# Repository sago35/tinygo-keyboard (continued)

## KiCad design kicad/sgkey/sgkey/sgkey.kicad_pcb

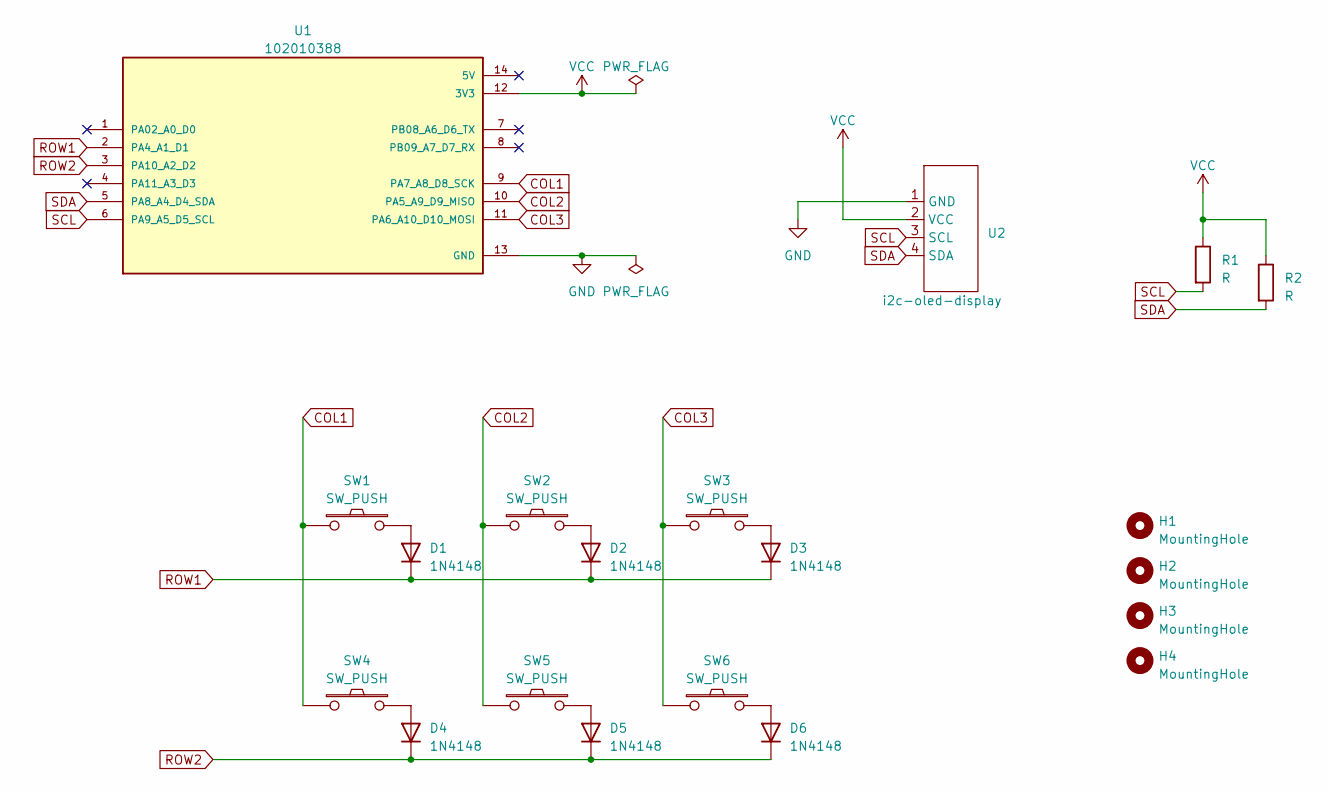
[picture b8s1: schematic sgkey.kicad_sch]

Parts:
D1, D2, D3, D4, D5, D6: 1N4148; D_DO-35_SOD27_P7.62mm_Horizontal
H1, H2, H3, H4: MountingHole; MountingHole_2.2mm_M2
R1, R2: R; R_Axial_DIN0204_L3.6mm_D1.6mm_P7.62mm_Horizontal
SW1, SW2, SW3, SW4, SW5, SW6: SW_PUSH; CherryMX_ChocV2_1u
U1: 102010388; MODULE_102010388; PARTREV N/A
U2: i2c-oled-display; i2c-oled-display-0.96

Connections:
COL1: SW1.1, SW4.1, U1.9 (PA7_A8_D8_SCK)
COL2: SW2.1, SW5.1, U1.10 (PA5_A9_D9_MISO)
COL3: SW3.1, SW6.1, U1.11 (PA6_A10_D10_MOSI)
GND: U1.13 (GND), U2.1 (GND)
unnamed: D1.2 (A), SW1.2
unnamed: D2.2 (A), SW2.2
unnamed: D3.2 (A), SW3.2
unnamed: D4.2 (A), SW4.2
unnamed: D5.2 (A), SW5.2
unnamed: D6.2 (A), SW6.2
ROW1: D1.1 (K), D2.1 (K), D3.1 (K), U1.2 (PA4_A1_D1)
ROW2: D4.1 (K), D5.1 (K), D6.1 (K), U1.3 (PA10_A2_D2)
SCL: R1.2, U1.6 (PA9_A5_D5_SCL), U2.3 (SCL)
SDA: R2.2, U1.5 (PA8_A4_D4_SDA), U2.4 (SDA)
VCC: R1.1, R2.1, U1.12 (3V3), U2.2 (VCC)

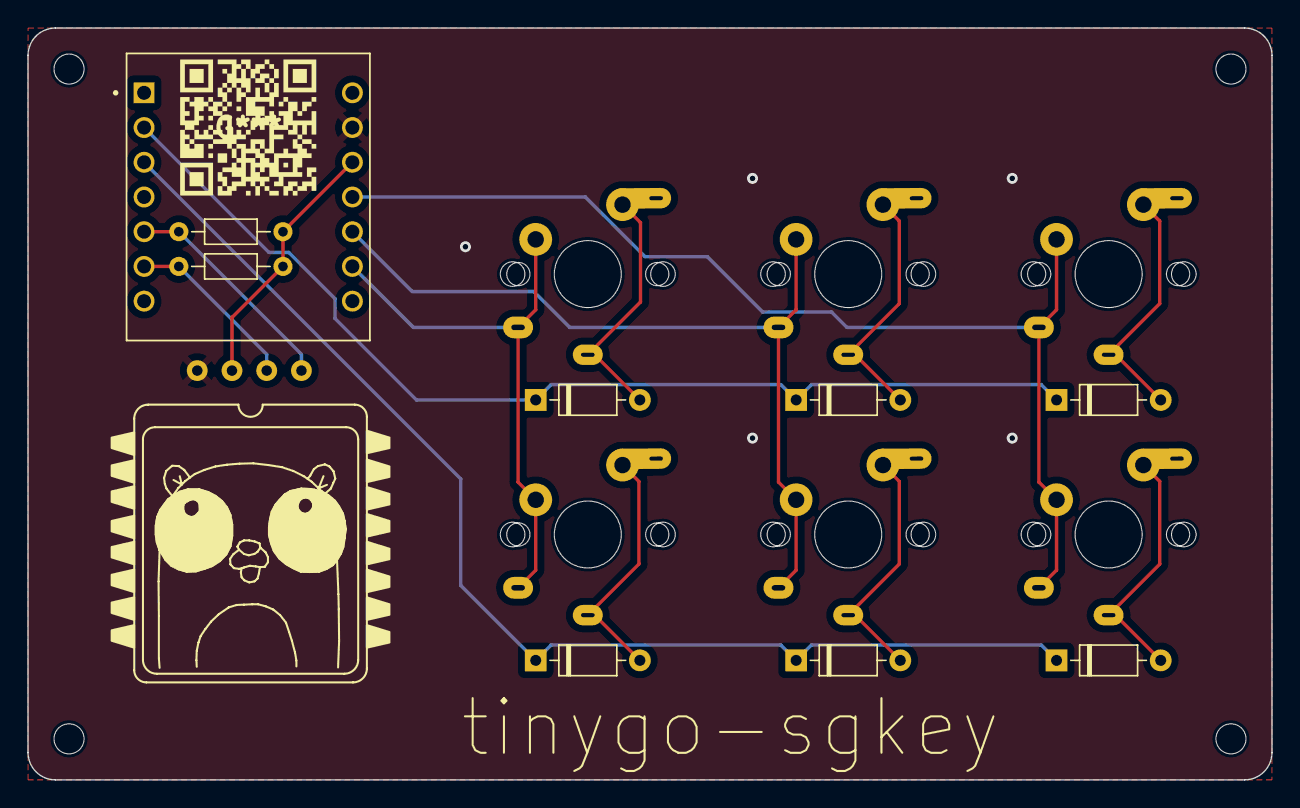
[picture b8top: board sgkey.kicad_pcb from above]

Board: 2 copper layers, 91.0 x 55.0 mm, 20 parts (0 on the bottom side), 15 nets.

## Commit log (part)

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2023-03-24 Fix behavior of `mod + ctrl`
2023-03-24 Add ./kicad
2023-03-24 Add Makefile
2023-03-24 Add kiicad/sgkey and kicad/wiokey
2023-03-24 Add smoketest
2023-04-04 Add fric10key
2023-04-08 Update ./targets/sgkb/left
2023-04-08 Add .gitignore
2023-04-09 Refactor (#2)
    refactor
2023-04-09 Add GpioKeyboard
2023-04-09 Add RotaryKeyboard
2023-04-09 Fix UartKeyboard
2023-04-10 Fix UartKeyboard state transitions
2023-04-10 Refactor
2023-04-10 Update targets/macropad-rp2040
2023-04-10 Add forward and back buttons to Mouse
2023-04-10 Update targets/sgkb/left
2023-04-13 Add kbmatrix.go
2023-04-13 Add ./targets/fric10key
2023-04-16 Add build tag to kbrotary.go
2023-04-17 Add options.go
2023-04-17 Add build tag
2023-04-17 Add test for `go get`
2023-04-17 Add InvertButtonState option
2023-04-17 Update targets/wiokey
2023-05-18 Update targets/sgkey
2023-05-18 Add InvertDiode option
2023-05-18 Update kicad/wiokey
2023-05-21 Add targets/sgkey/README.md
2023-05-23 Update kicad/sgkb and kicad/sgkb-right
2023-06-08 Add SetCallback()
2023-06-08 go mod
2023-06-08 Add ./targets/gopher-badge
2023-06-13 Fix nil pointer dereference
2023-06-13 Add display support for ./targets/sgkey
2023-06-13 Update README (sgkb-0.3.0)
2023-06-13 Update Makefile
2023-06-13 Update README.md (add gopher-badge)
2023-06-23 Improve key detection by pullups of kbduplexmatrix
2023-07-10 Add kicad/xiao-kb01
2023-07-10 Add kbsquaredmatrix.go
2023-07-10 Add targets/xiao-kb01
2023-07-10 Update targets/xiao-kb01
2023-07-15 Add kicad/xiao-kb01/xiao-kb01-top
2023-07-15 Add kicad/lib/xiao/CherryMX_ChocV2_1u_with_2u_stabilizer
2023-07-15 sgkb 0.4.0
2023-07-16 WIP: targets/sgkey
2023-07-17 MO(0) ～ MO(5) に対応
2023-07-17 WIP: kbd.Load() の引数変更に対応
2023-07-25 sgkb-0.4.0
2023-07-26 Update kicad library path
2023-07-26 Add kicad/lib/xiao/CherryMX_Hotswap_top.kicad_mod
2023-08-04 Support sgkb-0.4.0
2023-08-05 Add targets/sgkb/left-0.3.0
2023-08-05 Update callback
2023-08-05 Update kbuart.go and ./targets/sgkb/right
2023-08-05 WIP: vial
2023-08-06 Add SetKeycode()
2023-08-06 Add keyboardDef to targets/sgkb/left-0.3.0
2023-08-06 Add support for vial (read layout)
2023-08-06 WIP: vial.json を embed で読み込むように修正
2023-08-08 Add vial settings
2023-08-08 Refactor KeyVia()
2023-08-12 Add vial support for ./targets/sgkey
2023-08-14 WIP: save
2023-08-15 Add comment
2023-08-15 Add checks to prevent out-of-index access
2023-08-15 Change to store settings to machine.Flash
2023-08-15 Add TODO comment
2023-08-15 Move flash write to Tick()
2023-08-15 Add vial support to macropad-rp2040 and gopher-badge
2023-08-19 Refactore keybords and keys settings
2023-08-19 Add vial support to ./targets/xiao-kb01
2023-08-19 implement generating def.go
2023-08-19 copy def.go
2023-08-19 add lzma example to ./cmd
2023-08-19 add gen-def command to Makefile
2023-08-19 update keyboard-def
2023-08-19 add gen-def of xiao-kb01
2023-08-19 mkdir ./cmd/gen-def
2023-08-19 add xiao-kb01/def.go
2023-08-20 fix imports
2023-08-20 add `make gen-def-with-find` command
2023-08-20 Add `make gen-def` (#4)
2023-08-23 Remove `//go:embed vial.json`
2023-08-23 Update vial.json (rows / cols)
2023-08-23 Vial (#5)
2023-08-23 Add .github/workflows/ci.yml
2023-08-23 Add .github/workflows/ci.yml (#6)
2023-08-23 Remove heap allocs
2023-08-23 Set keycode 0x7C03 to a special keycode for restoring default
2023-09-01 Optimize number of keys
2023-09-01 Update targets
2023-09-01 Remove unused const value
2023-09-08 Add tutorial
2023-09-14 Add vial support to wiokey
2023-09-14 Add feature to restore key settings to default values
2023-09-15 Add chattering prevention
2023-09-22 Fix chattering prevention without blocking operation for kbduplexmatrix
2023-09-22 Remove blocking oparation
2023-10-10 Improved chattering prevention
2023-10-12 Add kbshifter.go
2023-10-12 Add ./targets/gobadge/
2023-10-17 Consolidate key modifier constants
2023-10-17 Add support for To(x)
2023-10-17 Update targets/gobadge
2023-10-17 vial
2023-10-17 Add Cyclecounter initialization
2023-10-17 Add chattering prevention when changing from None to NoneToPress
2023-10-22 Change variable name
2023-10-30 Add chattering prevention (#13)
    * Add chattering prevention
    * Fix chattering prevention without blocking operation for kbduplexmatrix
    * Remove blocking oparation
    * Improved chattering prevention
    * Add Cyclecounter initialization
    * Add chattering prevention when changing from None to NoneToPress
2023-10-30 Add debounce support for kbgpio, kbmatrix, kbsquaredmatrix
2023-10-30 Add debounce support for kbgpio, kbmatrix, kbsquaredmatrix (#17)
    * Add debounce support for kbgpio, kbmatrix, kbsquaredmatrix
    * fix
2023-10-30 initial bluetooth support between split keyboards
2023-10-31 Extend CI triggers to include pull requests
2023-10-31 Extend CI triggers to include pull requests (#19)
    * Extend CI triggers to include pull requests
2023-10-31 Change to pass through ringbuffer
2023-10-31 WIP: Add targets/sgkey-ble
2023-11-08 go get github.com/bgould/tinygo-rotary-encoder
2023-11-08 Add magic word for vial-gui
2023-11-14 Add ./ble for BLE HID Keyboard
2023-11-14 Remove
2023-11-14 Truncate to 14 characters
2023-11-14 Copy from TinyGo 0.30.0
2023-11-14 Change to send data to blehid instead of usbhid
2023-11-14 Change the reportMap to the same one as used for USB
2023-11-14 Add ./targets/sgkey2
2023-11-16 Update ./targets/sgkey2
2023-11-16 Add ./targets/xiao-kb012/
2023-11-16 Remove comments
2023-12-05 Update ./kicad/lib/
2023-12-05 Add ./kicad/sgh60/
2023-12-05 Add ./targets/sgh60/
2023-12-26 Update ./targets/sgh60/
2023-12-26 Add d.Layer()
2023-12-26 Add ./targets/sgh60/adcdevice.go
2023-12-26 Fix Makefile
2023-12-26 Add ticker for loop interval and removed static sleep in keyboard loop
2023-12-26 Add ./targets/sg48key/
2023-12-26 Add ./targets/sg48key/ (#23)
2023-12-26 Update README.md (#24)
2023-12-26 rename
2023-12-26 Update README.md (#25)
2024-01-01 Refactor keycodes
2024-01-01 Refactor callbacks
2024-01-01 refactor layers
2024-01-01 revert
2024-01-01 Add keyrepeat function to WheelDown / WheelUp
2024-01-16 Several improvements (#26)
    * Changed the timing of callbacks to occur after key processing.
    * Organized key code definitions.
    * Set key repeat for mouse wheel events.
    * Changed the behavior to remember the return destination using a stack when transitioning layers.
2024-01-16 Fix due to debounce not working
2024-01-16 Fix due to debounce not working (#27)
2024-01-30 Change processing interval to 1ms and debounce handling to 1ms x 8 times
2024-01-30 Update ./targets
2024-01-30 Update targets (#29)
2024-01-30 Update kicad/lib/xiao
2024-01-30 Update lib
2024-01-30 Add kicad/sg24key
2024-02-05 Add suport for Vial's Matrix tester
2024-02-05 Add suport for Vial's Matrix tester (#30)
2024-02-15 Add xiao-rp2040 for sg48key, improve joystick
2024-02-15 Add xiao-rp2040 for sg48key, improve joystick (#32)
2024-02-20 Update actions/*
2024-02-20 Update actions/* (#33)
2024-02-28 Add magic word for vial-gui (#21)
2024-02-29 kbrotary: switch to use tinygo-org/drivers v0.27.0
2024-02-29 Add buildtag to kbrotary.go
2024-02-29 kbrotary: switch to use tinygo-org/drivers v0.27.0 (#37)
    * kbrotary: switch to use tinygo-org/drivers v0.27.0
    * go mod
    * Add buildtag to kbrotary.go
2024-02-29 Add CHANGELOG.md
2024-03-19 WIP: BLEHID
2024-04-15 WIP: uart mouse
2024-04-16 Add support for vial macros
2024-04-16 Increase delay for save operation from 500ms to 5000ms
2024-06-17 implemented kbexpander
2024-07-07 Add `Additional Resources` to README.md
2024-07-10 stuff
2024-07-11 updated stuff
2024-07-11 more stuff
2024-07-18 Add device.GetKeyboardCount()
2024-07-18 Add device.GetKeyboardCount() (#43)
2024-07-25 updated module
2024-07-28 Fixed kbexpander and reduced debounce time
2024-07-28 Removed own keyboard
2024-07-28 Removed debug log prints
2024-07-28 Added explicitly ignoring possible errors
2024-07-28 Added IO-Expander keyboard
2024-07-29 Started to implement vialrgb currently working on usb-get part
2024-07-30 Continued implementation, need to finish writing part
2024-07-31 Added IO-Expander keyboard (#44)
2024-07-31 Add KeyMediaBrightnessDown and KeyMediaBrightnessUp
2024-08-01 Add KeyMediaBrightnessDown and KeyMediaBrightnessUp (#45)
2024-08-01 Finished untested vialrgb communication
2024-08-02 Finished untested vialrgb implementation with a few animations
2024-08-02 Made struct elements public
2024-08-07 Fixed RGB communication
2024-08-13 Finished RGB implementation TODO: test remembering vial settings
2024-08-15 Fixed saving and loading rgb settings
2024-08-15 Implemented new rgb animation
2024-08-15 Implemented gradient rgb effect
2024-08-16 implemented Breathing effect, TODO: rework animation speed
2024-08-18 adding comment to rgb.go to pass ci
2024-09-02 support newer tinygo-org/bluetooth
2024-10-06 Fix the issue where `time.Tick` was not working properly
2024-10-06 Fix the issue where `time.Tick` was not working properly (#49)
2024-10-07 reworkted animation speed for breathing animation
2024-10-07 implemented 4/6 Band Animations
2024-10-07 implemented 6/6 Band Animations
2024-10-07 implemented All Cycle Animations
2024-10-07 implemented All Beacon Animations
2024-10-07 implemented All Animations that are no rain or reactive effects
2024-11-19 Add support for Vial's combos
2024-11-19 Update README.md and Makefile
2024-11-19 Update ./targets/macropad-rp2040
2024-11-19 Change the operation of ws2812 to use piolib
2024-11-19 Update parameter of ADCDevice
2024-11-20 Update parameter of ADCDevice (#52)
2024-11-21 Remove the dependency on the keycodes/jp package from tinygo-keyboard
2024-11-21 Fix the behavior of Macros in the Japanese layout
2024-12-07 Rename keycodes/jp to keycodes/japanese
2024-12-07 Rename keycodes/jp to keycodes/japanese (#55)
2024-12-09 Change the timing for deactivating Combos
2024-12-09 Change the timing for deactivating Combos (#56)
2024-12-09 Fix and improve var names
2024-12-09 Fix and improve var names (#57)
2024-12-10 Replace magic numbers with the enum names used in via and vial
2024-12-10 Replace magic numbers with the enum names used in via and vial (#58)
2024-12-11 Add support for MediaKeys (Mute, Stop, Play)
2024-12-12 Add support for MediaKeys (Mute, Stop, Play) (#59)
2024-12-12 Improve to avoid heap allocation
2024-12-12 Improve to avoid heap allocation (#60)
2024-12-18 Add implementation for Mod-Tap and Modifier Keys
2024-12-18 Add implementation for Mod-Tap and Modifier Keys (#61)
2024-12-23 Fix index-out-of-range
2024-12-23 Fix index-out-of-range (#62)
2024-12-24 Fix an issue where the `OutputKey` was incorrect when multiple Combos were configured
2024-12-24 Fix the press order when cancelling Combos
2024-12-24 Fix an issue where the `OutputKey` was incorrect when multiple Combos were configured (#63)
2024-12-24 Fix the press order when cancelling Combos (#64)
2024-12-24 Add an interface to configure Combos
2025-01-03 Add an interface to configure Combos (#65)
2025-01-03 Update ./targets/sg48key/ and ./targets/sgh60/
2025-01-21 Fix I2C configuration for xiao-rp2040 and xiao-ble
2025-02-12 Modify to allow setting macros from code
2025-02-12 Add an example of using SetMacro()
2025-02-14 Add missing key definitions to keycodes/japanese
2025-02-14 Update ./targets/sgkey
2025-02-17 Add italian keycodes
2025-02-27 Implement AltGrMask support
    taken from https://github.com/tinygo-org/tinygo/blob/52983794d702af7a00833ae12b0d2e7175e46017/src/machine/usb/hid/keyboard/keycode.go#L233
2025-02-28 Fix typo
2025-09-01 Adapt to *ssd1306.Device change
2025-09-01 Update CHANGELOG.md (#72)
2025-09-18 Replace hardcoded USB endpoint numbers with named constants for readability
2025-09-18 Replace hardcoded USB endpoint numbers with named constants for readability (#73)
2026-02-13 Make index calculation customizable in SquaredMatrixKeyboard
2026-02-13 Make index calculation customizable in SquaredMatrixKeyboard (#74)
2026-02-28 board: add build tag for rp2350 so code can be build for xiao-rp2350
2026-03-04 board: add build tag for rp2350 so code can be build for xiao-rp2350 (#75)
2026-06-26 Replace endpoint configuration with a hardcoded value
2026-06-28 Replace endpoint configuration with a hardcoded value (#76)
2026-06-28 Update key-mapping
